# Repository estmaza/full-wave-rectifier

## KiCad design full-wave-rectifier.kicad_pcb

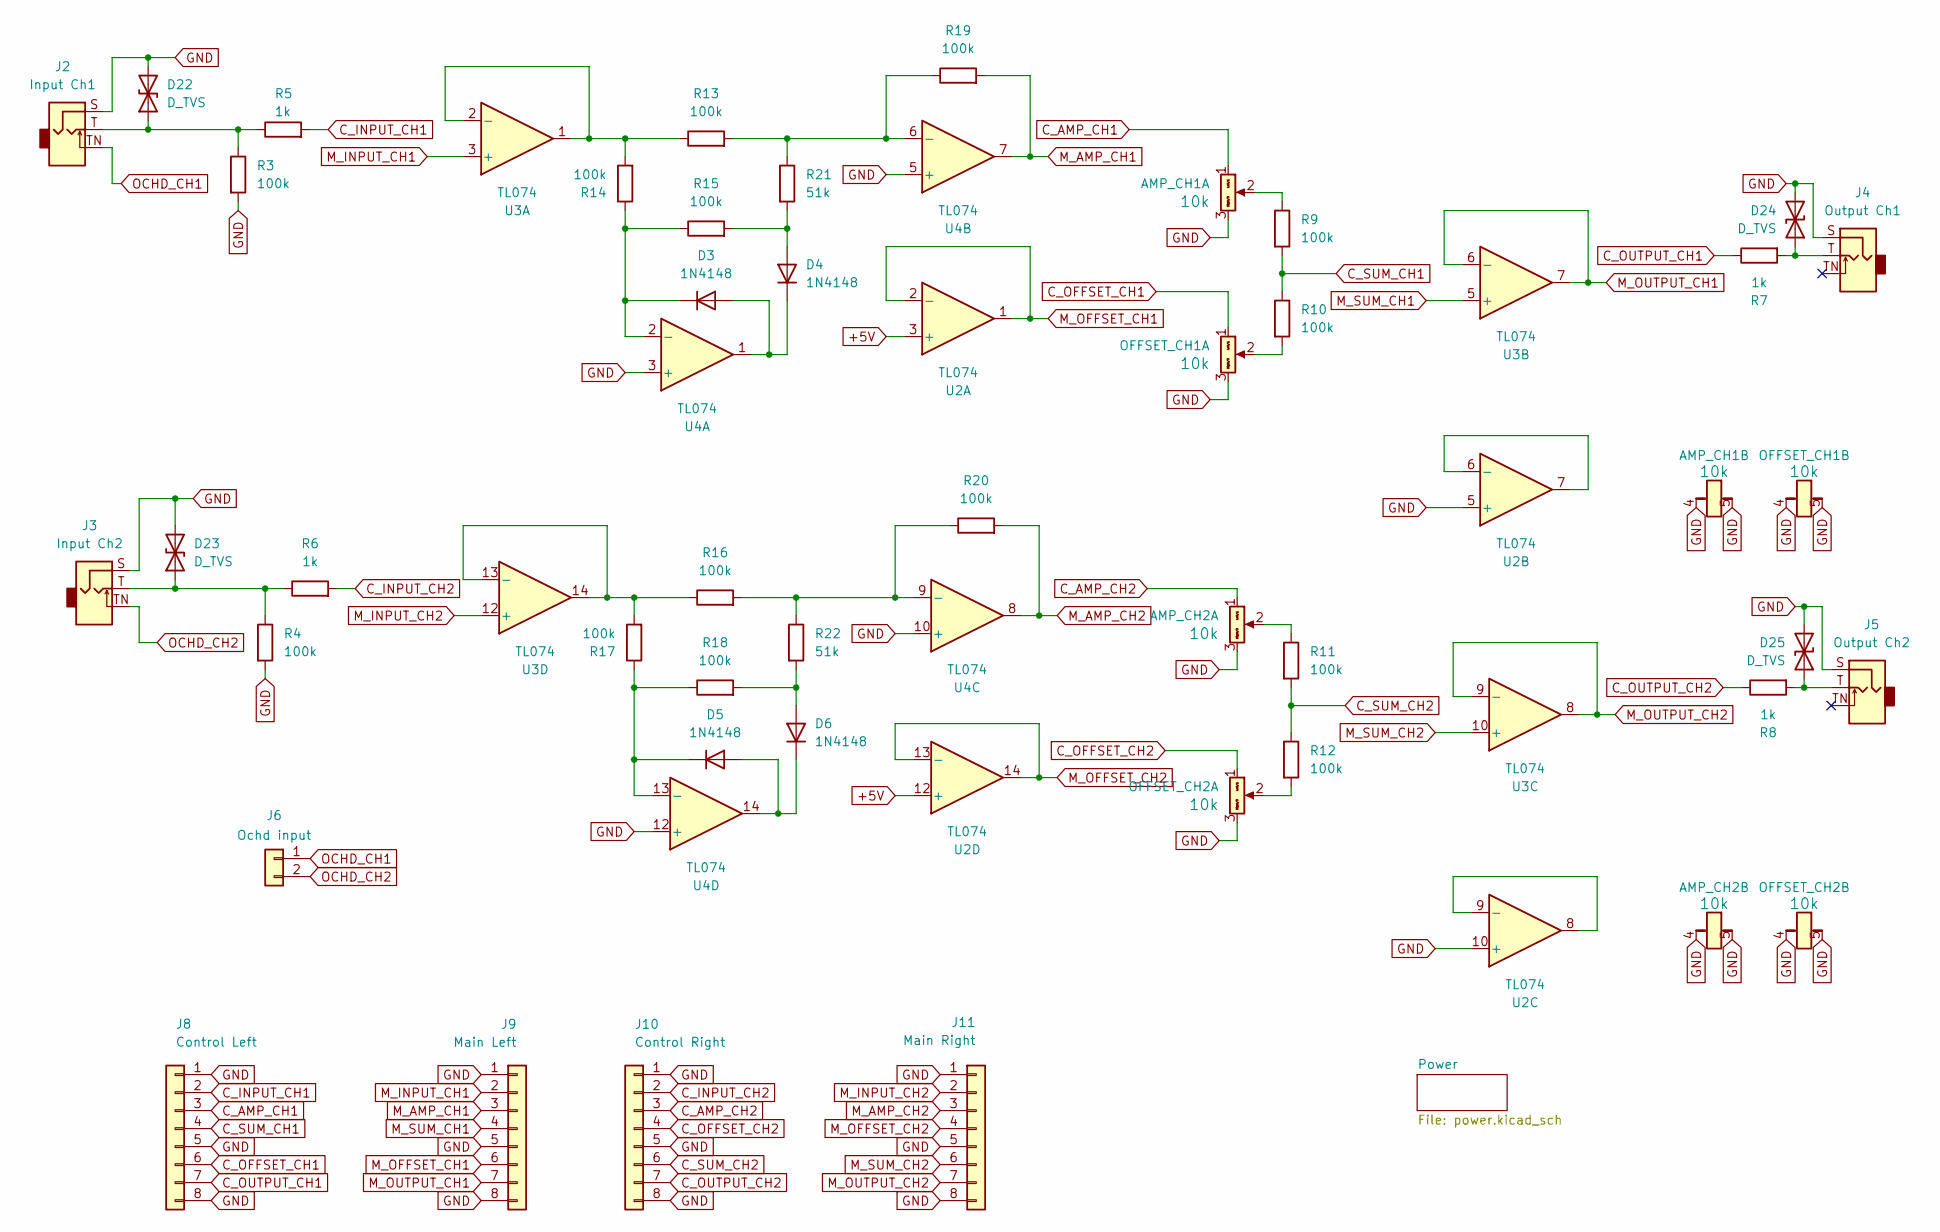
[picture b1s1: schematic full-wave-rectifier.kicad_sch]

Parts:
AMP_CH1, AMP_CH2: 10k; Pot_Alpha_9mm; Part Number RV09BCF-40-25F-B10K-007
D3, D4, D5, D6: 1N4148; D_SOD-123_Metric1.30x1.75mm_HandSolder
D22, D23, D24, D25: D_TVS; D_SOD-323_HandSoldering
J2: Input Ch1; Jack_3.5mm_WQP518MA
J3: Input Ch2; Jack_3.5mm_WQP518MA
J4: Output Ch1; Jack_3.5mm_WQP518MA
J5: Output Ch2; Jack_3.5mm_WQP518MA
J6: Ochd input; PinHeader_1x02_P2.54mm_Vertical
J8: Control Left; PinSocket_1x08_P2.54mm_Vertical
J9: Main Left; PinHeader_1x08_P2.54mm_Vertical
J10: Control Right; PinSocket_1x08_P2.54mm_Vertical
J11: Main Right; PinHeader_1x08_P2.54mm_Vertical
OFFSET_CH1, OFFSET_CH2: 10k; Pot_Alpha_9mm; Part Number RV09BCF-40-25F-B10K-007
R3, R4, R9, R10, R11, R12, R13, R14, R15, R16, R17, R18, R19, R20: 100k; R_1206_3216Metric_Pad1.30x1.75mm_HandSolder; Part Number 299-100k-RC
R5, R6, R7, R8: 1k; R_1206_3216Metric_Pad1.30x1.75mm_HandSolder; Part Number 299-1k-RC
R21, R22: 51k; R_1206_3216Metric_Pad1.30x1.75mm_HandSolder; Part Number 299-51k-RC
U2, U3, U4: TL074; SOIC-14_3.9x8.7mm_P1.27mm

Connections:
+5V: U2.3 (+), U2.12 (+); also elsewhere on the board
GND: AMP_CH1.3 (Right), AMP_CH1.4 (Tab1), AMP_CH1.5 (Tab2), AMP_CH2.3 (Right), AMP_CH2.4 (Tab1), AMP_CH2.5 (Tab2), D22.2 (A2), D23.2 (A2), D24.2 (A2), D25.2 (A2), J2.S, J3.S, J4.S, J5.S, J8.1, J8.5, J8.8, J9.1, J9.5, J9.8, J10.1, J10.5, J10.8, J11.1, J11.5, J11.8, OFFSET_CH1.3 (Right), OFFSET_CH1.4 (Tab1), OFFSET_CH1.5 (Tab2), OFFSET_CH2.3 (Right), OFFSET_CH2.4 (Tab1), OFFSET_CH2.5 (Tab2), R3.2, R4.2, U2.5 (+), U2.10 (+), U4.3 (+), U4.5 (+), U4.10 (+), U4.12 (+); also elsewhere on the board
M_AMP_CH1: J9.3, R19.2, U4.7
M_AMP_CH2: J11.3, R20.2, U4.8
M_INPUT_CH1: J9.2, U3.3 (+)
M_INPUT_CH2: J11.2, U3.12 (+)
M_OFFSET_CH1: J9.6, U2.1, U2.2 (-)
M_OFFSET_CH2: J11.4, U2.13 (-), U2.14
M_OUTPUT_CH1: J9.7, U3.6 (-), U3.7
M_OUTPUT_CH2: J11.7, U3.8, U3.9 (-)
M_SUM_CH1: J9.4, U3.5 (+)
M_SUM_CH2: J11.6, U3.10 (+)
unnamed: AMP_CH1.2 (Center), R9.1
unnamed: AMP_CH2.2 (Center), R11.1
unnamed: D3.2 (A), D4.1 (K), U4.1
unnamed: D3.1 (K), R14.1, R15.1, U4.2 (-)
unnamed: D4.2 (A), R15.2, R21.2
unnamed: D5.2 (A), D6.1 (K), U4.14
unnamed: D5.1 (K), R17.1, R18.1, U4.13 (-)
unnamed: D6.2 (A), R18.2, R22.2
unnamed: D22.1 (A1), J2.T, R3.1, R5.1
unnamed: D23.1 (A1), J3.T, R4.1, R6.1
unnamed: D24.1 (A1), J4.T, R7.2
unnamed: D25.1 (A1), J5.T, R8.2
unnamed: OFFSET_CH1.2 (Center), R10.2
unnamed: OFFSET_CH2.2 (Center), R12.2
unnamed: U2.6 (-), U2.7
unnamed: U2.8, U2.9 (-)
unnamed: R13.1, R14.2, U3.1, U3.2 (-)
unnamed: R16.1, R17.2, U3.13 (-), U3.14
unnamed: R13.2, R19.1, R21.1, U4.6 (-)
unnamed: R16.2, R20.1, R22.1, U4.9 (-)
OCHD_CH1: J2.TN, J6.1
OCHD_CH2: J3.TN, J6.2
С_AMP_CH1: AMP_CH1.1 (Left), J8.3
С_AMP_CH2: AMP_CH2.1 (Left), J10.3
С_INPUT_CH1: J8.2, R5.2
С_INPUT_CH2: J10.2, R6.2
С_OFFSET_CH1: J8.6, OFFSET_CH1.1 (Left)
С_OFFSET_CH2: J10.4, OFFSET_CH2.1 (Left)
С_OUTPUT_CH1: J8.7, R7.1
С_OUTPUT_CH2: J10.7, R8.1
С_SUM_CH1: J8.4, R9.2, R10.1
С_SUM_CH2: J10.6, R11.2, R12.1

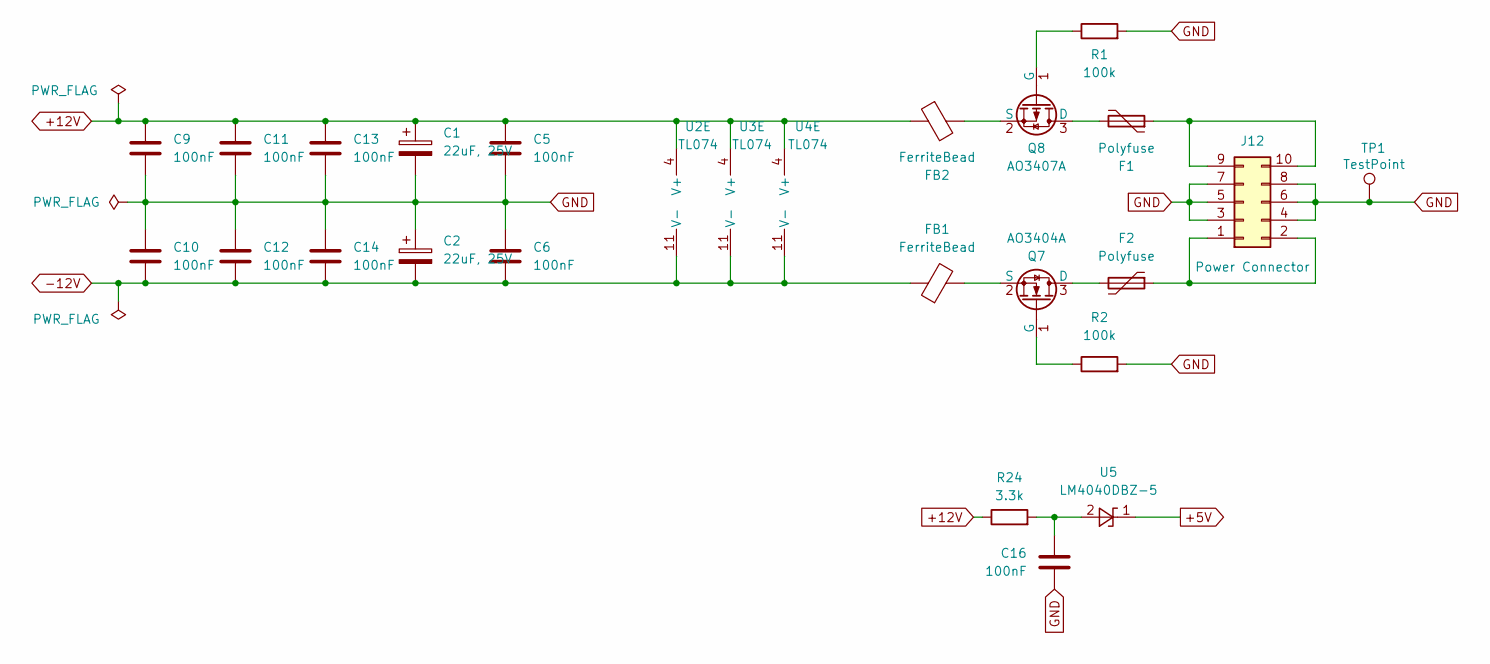
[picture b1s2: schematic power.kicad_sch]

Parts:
C1, C2: 22uF, 25V; CP_Elec_5x5.8
C5, C6, C9, C10, C11, C12, C13, C14, C16: 100nF; C_1206_3216Metric_Pad1.33x1.80mm_HandSolder
F1, F2: Polyfuse; Fuse_1206_3216Metric_Pad1.42x1.75mm_HandSolder
FB1, FB2: FerriteBead; L_1206_3216Metric_Pad1.22x1.90mm_HandSolder
J12: Power Connector; IDC-Header_2x05_P2.54mm_Vertical
Q7: AO3404A; SOT-23_Handsoldering
Q8: AO3407A; SOT-23_Handsoldering
R1, R2: 100k; R_1206_3216Metric_Pad1.30x1.75mm_HandSolder
R24: 3.3k; R_1206_3216Metric_Pad1.30x1.75mm_HandSolder
TP1: TestPoint; TestPoint_THTPad_2.0x2.0mm_Drill1.0mm
U2, U3, U4: TL074; SOIC-14_3.9x8.7mm_P1.27mm
U5: LM4040DBZ-5; SOT-23_Handsoldering

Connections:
+5V: U5.1 (K); also elsewhere on the board
+12V: C1.1, C5.1, C9.1, C11.1, C13.1, FB2.1, R24.1, U2.4 (V+), U3.4 (V+), U4.4 (V+)
-12V: C2.2, C6.2, C10.2, C12.2, C14.2, FB1.1, U2.11 (V-), U3.11 (V-), U4.11 (V-)
GND: C1.2, C2.1, C5.2, C6.1, C9.2, C10.1, C11.2, C12.1, C13.2, C14.1, C16.2, J12.3 (GND), J12.4 (GND), J12.5 (GND), J12.6 (GND), J12.7 (GND), J12.8 (GND), R1.2, R2.2, TP1.1 (1_1); also elsewhere on the board
unnamed: F1.1, J12.9 (+12V), J12.10 (+12V)
unnamed: F2.1, J12.1 (-12V), J12.2 (-12V)
unnamed: F2.2, Q7.3 (D)
unnamed: Q7.1 (G), R2.1
unnamed: FB1.2, Q7.2 (S)
unnamed: F1.2, Q8.3 (D)
unnamed: Q8.1 (G), R1.1
unnamed: FB2.2, Q8.2 (S)
unnamed: C16.1, R24.2, U5.2 (A)

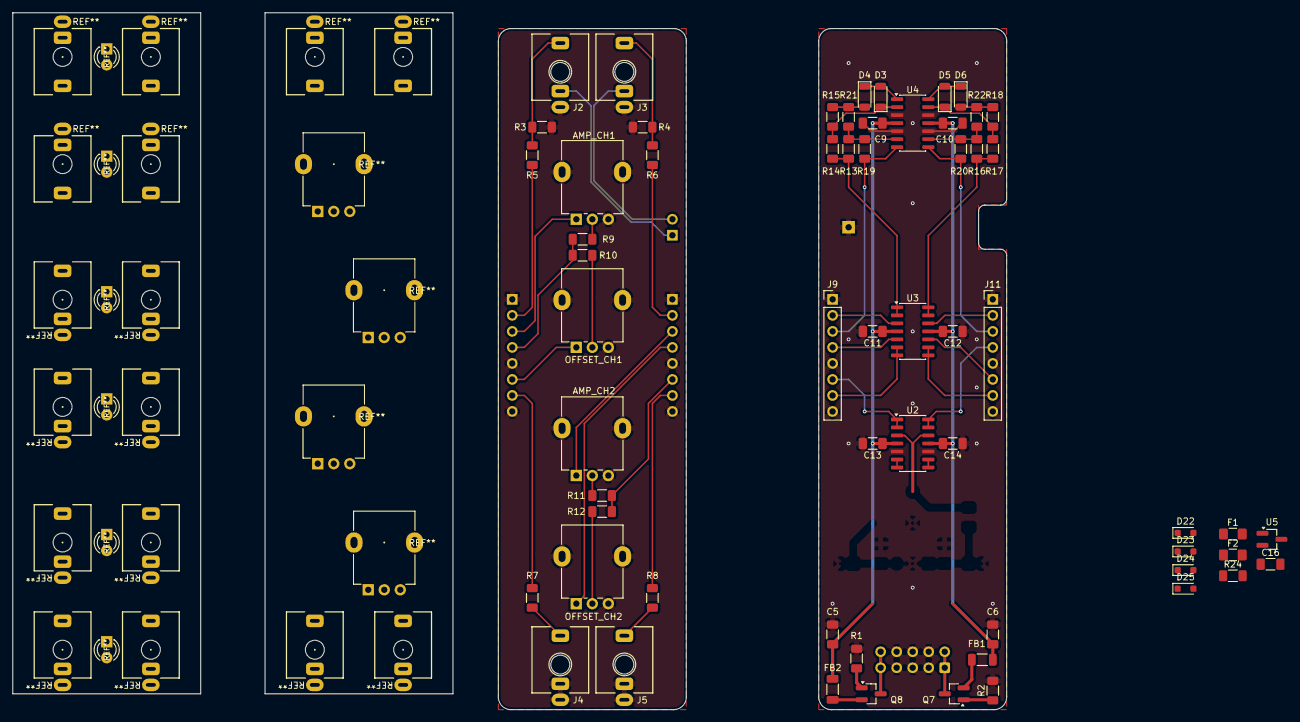
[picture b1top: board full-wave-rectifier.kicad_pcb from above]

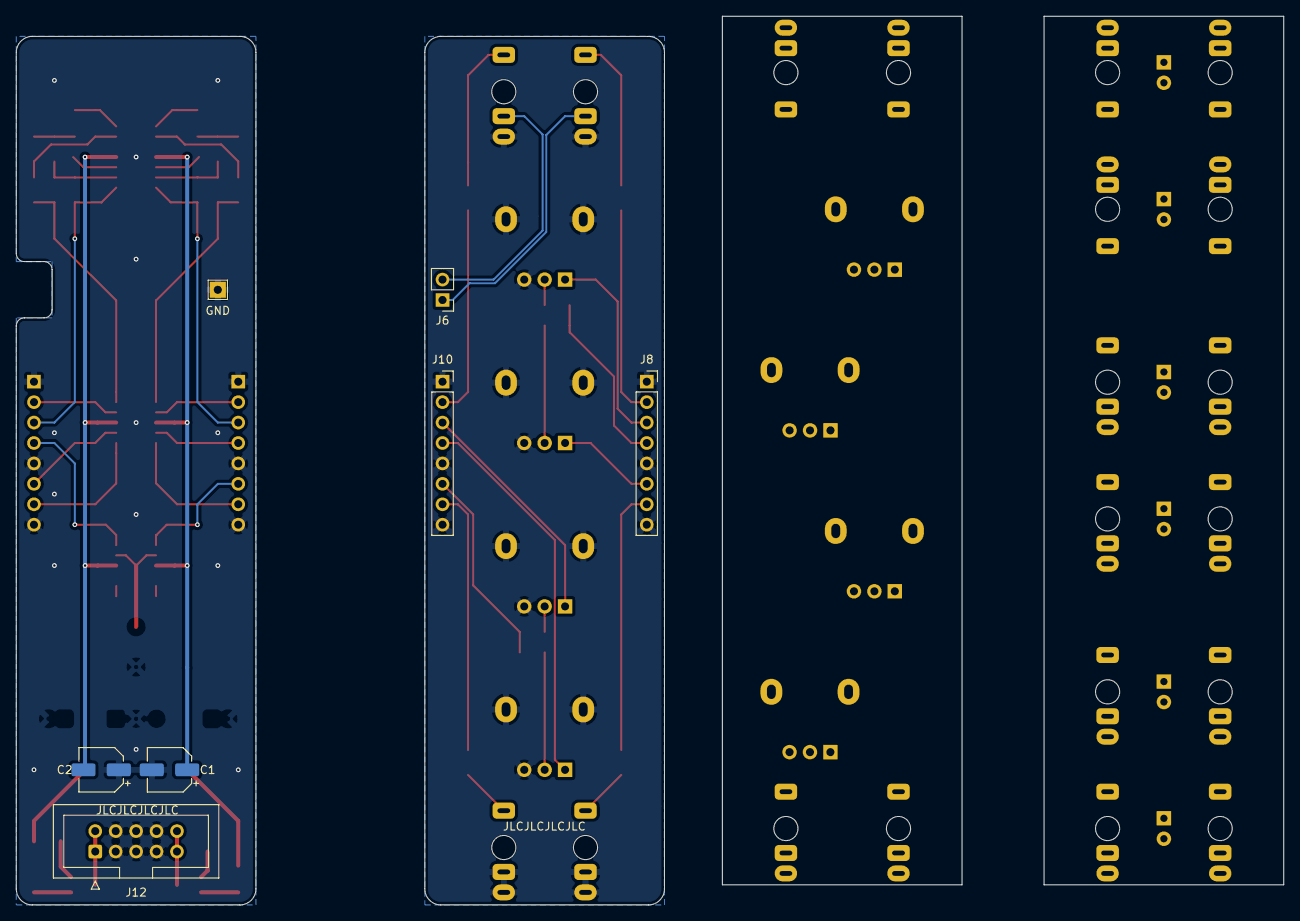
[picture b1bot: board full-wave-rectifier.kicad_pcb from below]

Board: 2 copper layers, 157.6 x 110.5 mm, 67 parts (7 on the bottom side), 55 nets.

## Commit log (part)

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2026-03-15 save changes
2026-03-16 power
2026-03-16 added rectifiers
2026-03-17 updated footprints
2026-03-17 Added faceplate template
2026-03-18 Initial faceplate design
2026-03-19 Added basic UI
2026-03-19 Sync sizes of both modules
2026-03-20 Updated footprint elements
2026-03-22 Updated control panel
2026-03-23 Updated layout
2026-03-23 fixed issue with Alpha pot legs
2026-03-23 Added test point
2026-03-23 fixed traces width
2026-03-23 faceplate
2026-03-23 fillet lines
2026-03-24 Added JLCJLCJLCJLC
2026-04-17 Updated power tracing
2026-05-06 save chages
